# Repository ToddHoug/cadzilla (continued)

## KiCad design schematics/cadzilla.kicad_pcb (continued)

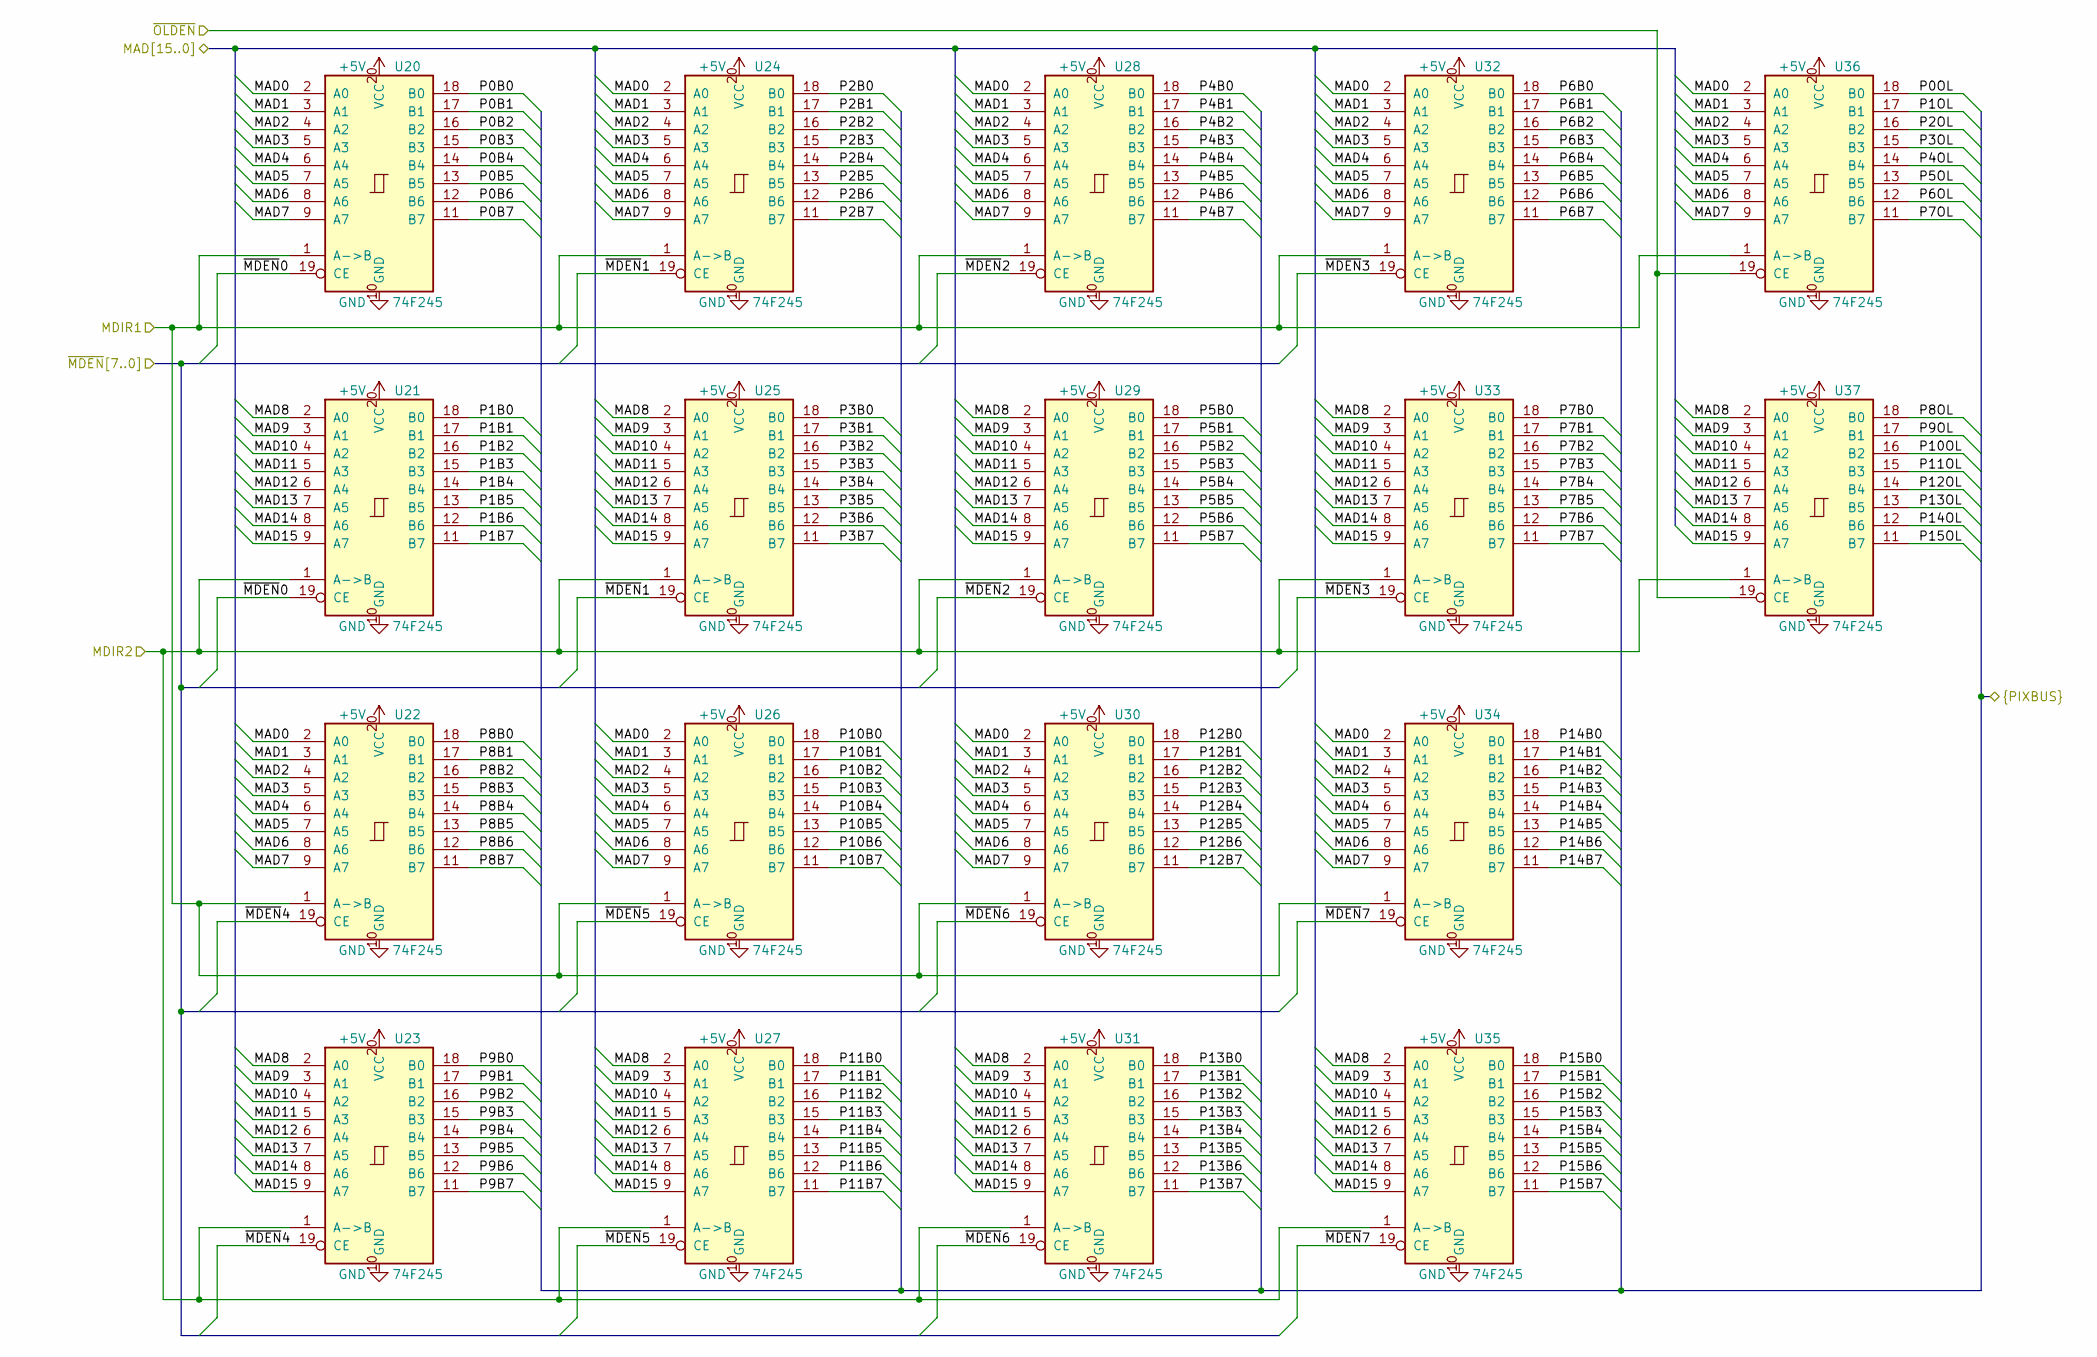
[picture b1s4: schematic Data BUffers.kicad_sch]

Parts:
U20, U21, U22, U23, U24, U25, U26, U27, U28, U29, U30, U31, U32, U33, U34, U35, U36, U37: 74F245; DIP-20_W7.62mm_Socket

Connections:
+5V: U20.20 (VCC), U21.20 (VCC), U22.20 (VCC), U23.20 (VCC), U24.20 (VCC), U25.20 (VCC), U26.20 (VCC), U27.20 (VCC), U28.20 (VCC), U29.20 (VCC), U30.20 (VCC), U31.20 (VCC), U32.20 (VCC), U33.20 (VCC), U34.20 (VCC), U35.20 (VCC), U36.20 (VCC), U37.20 (VCC); also elsewhere on the board
/Data Buffers/MAD0: U20.2 (A0), U22.2 (A0), U24.2 (A0), U26.2 (A0), U28.2 (A0), U30.2 (A0), U32.2 (A0), U34.2 (A0), U36.2 (A0); also elsewhere on the board
/Data Buffers/MAD1: U20.3 (A1), U22.3 (A1), U24.3 (A1), U26.3 (A1), U28.3 (A1), U30.3 (A1), U32.3 (A1), U34.3 (A1), U36.3 (A1); also elsewhere on the board
/Data Buffers/MAD2: U20.4 (A2), U22.4 (A2), U24.4 (A2), U26.4 (A2), U28.4 (A2), U30.4 (A2), U32.4 (A2), U34.4 (A2), U36.4 (A2); also elsewhere on the board
/Data Buffers/MAD3: U20.5 (A3), U22.5 (A3), U24.5 (A3), U26.5 (A3), U28.5 (A3), U30.5 (A3), U32.5 (A3), U34.5 (A3), U36.5 (A3); also elsewhere on the board
/Data Buffers/MAD4: U20.6 (A4), U22.6 (A4), U24.6 (A4), U26.6 (A4), U28.6 (A4), U30.6 (A4), U32.6 (A4), U34.6 (A4), U36.6 (A4); also elsewhere on the board
/Data Buffers/MAD5: U20.7 (A5), U22.7 (A5), U24.7 (A5), U26.7 (A5), U28.7 (A5), U30.7 (A5), U32.7 (A5), U34.7 (A5), U36.7 (A5); also elsewhere on the board
/Data Buffers/MAD6: U20.8 (A6), U22.8 (A6), U24.8 (A6), U26.8 (A6), U28.8 (A6), U30.8 (A6), U32.8 (A6), U34.8 (A6), U36.8 (A6); also elsewhere on the board
/Data Buffers/MAD7: U20.9 (A7), U22.9 (A7), U24.9 (A7), U26.9 (A7), U28.9 (A7), U30.9 (A7), U32.9 (A7), U34.9 (A7), U36.9 (A7); also elsewhere on the board
/Data Buffers/MAD8: U21.2 (A0), U23.2 (A0), U25.2 (A0), U27.2 (A0), U29.2 (A0), U31.2 (A0), U33.2 (A0), U35.2 (A0), U37.2 (A0); also elsewhere on the board
/Data Buffers/MAD9: U21.3 (A1), U23.3 (A1), U25.3 (A1), U27.3 (A1), U29.3 (A1), U31.3 (A1), U33.3 (A1), U35.3 (A1), U37.3 (A1); also elsewhere on the board
/Data Buffers/MAD10: U21.4 (A2), U23.4 (A2), U25.4 (A2), U27.4 (A2), U29.4 (A2), U31.4 (A2), U33.4 (A2), U35.4 (A2), U37.4 (A2); also elsewhere on the board
/Data Buffers/MAD11: U21.5 (A3), U23.5 (A3), U25.5 (A3), U27.5 (A3), U29.5 (A3), U31.5 (A3), U33.5 (A3), U35.5 (A3), U37.5 (A3); also elsewhere on the board
/Data Buffers/MAD12: U21.6 (A4), U23.6 (A4), U25.6 (A4), U27.6 (A4), U29.6 (A4), U31.6 (A4), U33.6 (A4), U35.6 (A4), U37.6 (A4); also elsewhere on the board
/Data Buffers/MAD13: U21.7 (A5), U23.7 (A5), U25.7 (A5), U27.7 (A5), U29.7 (A5), U31.7 (A5), U33.7 (A5), U35.7 (A5), U37.7 (A5); also elsewhere on the board
/Data Buffers/MAD14: U21.8 (A6), U23.8 (A6), U25.8 (A6), U27.8 (A6), U29.8 (A6), U31.8 (A6), U33.8 (A6), U35.8 (A6), U37.8 (A6); also elsewhere on the board
/Data Buffers/MAD15: U21.9 (A7), U23.9 (A7), U25.9 (A7), U27.9 (A7), U29.9 (A7), U31.9 (A7), U33.9 (A7), U35.9 (A7), U37.9 (A7); also elsewhere on the board
/Data Buffers/P0B0: U20.18 (B0); also elsewhere on the board
/Data Buffers/P0B1: U20.17 (B1); also elsewhere on the board
/Data Buffers/P0B2: U20.16 (B2); also elsewhere on the board
/Data Buffers/P0B3: U20.15 (B3); also elsewhere on the board
/Data Buffers/P0B4: U20.14 (B4); also elsewhere on the board
/Data Buffers/P0B5: U20.13 (B5); also elsewhere on the board
/Data Buffers/P0B6: U20.12 (B6); also elsewhere on the board
/Data Buffers/P0B7: U20.11 (B7); also elsewhere on the board
/Data Buffers/P0OL: U36.18 (B0); also elsewhere on the board
/Data Buffers/P1B0: U21.18 (B0); also elsewhere on the board
/Data Buffers/P1B1: U21.17 (B1); also elsewhere on the board
/Data Buffers/P1B2: U21.16 (B2); also elsewhere on the board
/Data Buffers/P1B3: U21.15 (B3); also elsewhere on the board
/Data Buffers/P1B4: U21.14 (B4); also elsewhere on the board
/Data Buffers/P1B5: U21.13 (B5); also elsewhere on the board
/Data Buffers/P1B6: U21.12 (B6); also elsewhere on the board
/Data Buffers/P1B7: U21.11 (B7); also elsewhere on the board
/Data Buffers/P1OL: U36.17 (B1); also elsewhere on the board
/Data Buffers/P2B0: U24.18 (B0); also elsewhere on the board
/Data Buffers/P2B1: U24.17 (B1); also elsewhere on the board
/Data Buffers/P2B2: U24.16 (B2); also elsewhere on the board
/Data Buffers/P2B3: U24.15 (B3); also elsewhere on the board
/Data Buffers/P2B4: U24.14 (B4); also elsewhere on the board
/Data Buffers/P2B5: U24.13 (B5); also elsewhere on the board
/Data Buffers/P2B6: U24.12 (B6); also elsewhere on the board
/Data Buffers/P2B7: U24.11 (B7); also elsewhere on the board
/Data Buffers/P2OL: U36.16 (B2); also elsewhere on the board
/Data Buffers/P3B0: U25.18 (B0); also elsewhere on the board
/Data Buffers/P3B1: U25.17 (B1); also elsewhere on the board
/Data Buffers/P3B2: U25.16 (B2); also elsewhere on the board
/Data Buffers/P3B3: U25.15 (B3); also elsewhere on the board
/Data Buffers/P3B4: U25.14 (B4); also elsewhere on the board
/Data Buffers/P3B5: U25.13 (B5); also elsewhere on the board
/Data Buffers/P3B6: U25.12 (B6); also elsewhere on the board
/Data Buffers/P3B7: U25.11 (B7); also elsewhere on the board
/Data Buffers/P3OL: U36.15 (B3); also elsewhere on the board
/Data Buffers/P4B0: U28.18 (B0); also elsewhere on the board
/Data Buffers/P4B1: U28.17 (B1); also elsewhere on the board
/Data Buffers/P4B2: U28.16 (B2); also elsewhere on the board
/Data Buffers/P4B3: U28.15 (B3); also elsewhere on the board
/Data Buffers/P4B4: U28.14 (B4); also elsewhere on the board
/Data Buffers/P4B5: U28.13 (B5); also elsewhere on the board
/Data Buffers/P4B6: U28.12 (B6); also elsewhere on the board
/Data Buffers/P4B7: U28.11 (B7); also elsewhere on the board
/Data Buffers/P4OL: U36.14 (B4); also elsewhere on the board
/Data Buffers/P5B0: U29.18 (B0); also elsewhere on the board
/Data Buffers/P5B1: U29.17 (B1); also elsewhere on the board
/Data Buffers/P5B2: U29.16 (B2); also elsewhere on the board
/Data Buffers/P5B3: U29.15 (B3); also elsewhere on the board
/Data Buffers/P5B4: U29.14 (B4); also elsewhere on the board
/Data Buffers/P5B5: U29.13 (B5); also elsewhere on the board
/Data Buffers/P5B6: U29.12 (B6); also elsewhere on the board
/Data Buffers/P5B7: U29.11 (B7); also elsewhere on the board
/Data Buffers/P5OL: U36.13 (B5); also elsewhere on the board
/Data Buffers/P6B0: U32.18 (B0); also elsewhere on the board
/Data Buffers/P6B1: U32.17 (B1); also elsewhere on the board
/Data Buffers/P6B2: U32.16 (B2); also elsewhere on the board
/Data Buffers/P6B3: U32.15 (B3); also elsewhere on the board
/Data Buffers/P6B4: U32.14 (B4); also elsewhere on the board
/Data Buffers/P6B5: U32.13 (B5); also elsewhere on the board
/Data Buffers/P6B6: U32.12 (B6); also elsewhere on the board
/Data Buffers/P6B7: U32.11 (B7); also elsewhere on the board
/Data Buffers/P6OL: U36.12 (B6); also elsewhere on the board
/Data Buffers/P7B0: U33.18 (B0); also elsewhere on the board
/Data Buffers/P7B1: U33.17 (B1); also elsewhere on the board
/Data Buffers/P7B2: U33.16 (B2); also elsewhere on the board
/Data Buffers/P7B3: U33.15 (B3); also elsewhere on the board
/Data Buffers/P7B4: U33.14 (B4); also elsewhere on the board
/Data Buffers/P7B5: U33.13 (B5); also elsewhere on the board
/Data Buffers/P7B6: U33.12 (B6); also elsewhere on the board
/Data Buffers/P7B7: U33.11 (B7); also elsewhere on the board
/Data Buffers/P7OL: U36.11 (B7); also elsewhere on the board
/Data Buffers/P8B0: U22.18 (B0); also elsewhere on the board
/Data Buffers/P8B1: U22.17 (B1); also elsewhere on the board
/Data Buffers/P8B2: U22.16 (B2); also elsewhere on the board
/Data Buffers/P8B3: U22.15 (B3); also elsewhere on the board
/Data Buffers/P8B4: U22.14 (B4); also elsewhere on the board
/Data Buffers/P8B5: U22.13 (B5); also elsewhere on the board
/Data Buffers/P8B6: U22.12 (B6); also elsewhere on the board
/Data Buffers/P8B7: U22.11 (B7); also elsewhere on the board
/Data Buffers/P8OL: U37.18 (B0); also elsewhere on the board
/Data Buffers/P9B0: U23.18 (B0); also elsewhere on the board
/Data Buffers/P9B1: U23.17 (B1); also elsewhere on the board
/Data Buffers/P9B2: U23.16 (B2); also elsewhere on the board
/Data Buffers/P9B3: U23.15 (B3); also elsewhere on the board
/Data Buffers/P9B4: U23.14 (B4); also elsewhere on the board
/Data Buffers/P9B5: U23.13 (B5); also elsewhere on the board
/Data Buffers/P9B6: U23.12 (B6); also elsewhere on the board
/Data Buffers/P9B7: U23.11 (B7); also elsewhere on the board
/Data Buffers/P9OL: U37.17 (B1); also elsewhere on the board
/Data Buffers/P10B0: U26.18 (B0); also elsewhere on the board
/Data Buffers/P10B1: U26.17 (B1); also elsewhere on the board
/Data Buffers/P10B2: U26.16 (B2); also elsewhere on the board
/Data Buffers/P10B3: U26.15 (B3); also elsewhere on the board
/Data Buffers/P10B4: U26.14 (B4); also elsewhere on the board
/Data Buffers/P10B5: U26.13 (B5); also elsewhere on the board
/Data Buffers/P10B6: U26.12 (B6); also elsewhere on the board
/Data Buffers/P10B7: U26.11 (B7); also elsewhere on the board
/Data Buffers/P10OL: U37.16 (B2); also elsewhere on the board
/Data Buffers/P11B0: U27.18 (B0); also elsewhere on the board
/Data Buffers/P11B1: U27.17 (B1); also elsewhere on the board
/Data Buffers/P11B2: U27.16 (B2); also elsewhere on the board
/Data Buffers/P11B3: U27.15 (B3); also elsewhere on the board
/Data Buffers/P11B4: U27.14 (B4); also elsewhere on the board
/Data Buffers/P11B5: U27.13 (B5); also elsewhere on the board
/Data Buffers/P11B6: U27.12 (B6); also elsewhere on the board
/Data Buffers/P11B7: U27.11 (B7); also elsewhere on the board
/Data Buffers/P11OL: U37.15 (B3); also elsewhere on the board
/Data Buffers/P12B0: U30.18 (B0); also elsewhere on the board
/Data Buffers/P12B1: U30.17 (B1); also elsewhere on the board
/Data Buffers/P12B2: U30.16 (B2); also elsewhere on the board
/Data Buffers/P12B3: U30.15 (B3); also elsewhere on the board
/Data Buffers/P12B4: U30.14 (B4); also elsewhere on the board
/Data Buffers/P12B5: U30.13 (B5); also elsewhere on the board
/Data Buffers/P12B6: U30.12 (B6); also elsewhere on the board
/Data Buffers/P12B7: U30.11 (B7); also elsewhere on the board
/Data Buffers/P12OL: U37.14 (B4); also elsewhere on the board
/Data Buffers/P13B0: U31.18 (B0); also elsewhere on the board
/Data Buffers/P13B1: U31.17 (B1); also elsewhere on the board
/Data Buffers/P13B2: U31.16 (B2); also elsewhere on the board
/Data Buffers/P13B3: U31.15 (B3); also elsewhere on the board
/Data Buffers/P13B4: U31.14 (B4); also elsewhere on the board
/Data Buffers/P13B5: U31.13 (B5); also elsewhere on the board
/Data Buffers/P13B6: U31.12 (B6); also elsewhere on the board
/Data Buffers/P13B7: U31.11 (B7); also elsewhere on the board
/Data Buffers/P13OL: U37.13 (B5); also elsewhere on the board
/Data Buffers/P14B0: U34.18 (B0); also elsewhere on the board
/Data Buffers/P14B1: U34.17 (B1); also elsewhere on the board
/Data Buffers/P14B2: U34.16 (B2); also elsewhere on the board
/Data Buffers/P14B3: U34.15 (B3); also elsewhere on the board
/Data Buffers/P14B4: U34.14 (B4); also elsewhere on the board
/Data Buffers/P14B5: U34.13 (B5); also elsewhere on the board
/Data Buffers/P14B6: U34.12 (B6); also elsewhere on the board
/Data Buffers/P14B7: U34.11 (B7); also elsewhere on the board
/Data Buffers/P14OL: U37.12 (B6); also elsewhere on the board
/Data Buffers/P15B0: U35.18 (B0); also elsewhere on the board
/Data Buffers/P15B1: U35.17 (B1); also elsewhere on the board
/Data Buffers/P15B2: U35.16 (B2); also elsewhere on the board
/Data Buffers/P15B3: U35.15 (B3); also elsewhere on the board
/Data Buffers/P15B4: U35.14 (B4); also elsewhere on the board
/Data Buffers/P15B5: U35.13 (B5); also elsewhere on the board
/Data Buffers/P15B6: U35.12 (B6); also elsewhere on the board
/Data Buffers/P15B7: U35.11 (B7); also elsewhere on the board
/Data Buffers/P15OL: U37.11 (B7); also elsewhere on the board
/Data Buffers/~MDEN0: U20.19 (CE), U21.19 (CE); also elsewhere on the board
/Data Buffers/~MDEN1: U24.19 (CE), U25.19 (CE); also elsewhere on the board
/Data Buffers/~MDEN2: U28.19 (CE), U29.19 (CE); also elsewhere on the board
/Data Buffers/~MDEN3: U32.19 (CE), U33.19 (CE); also elsewhere on the board
/Data Buffers/~MDEN4: U22.19 (CE), U23.19 (CE); also elsewhere on the board
/Data Buffers/~MDEN5: U26.19 (CE), U27.19 (CE); also elsewhere on the board
/Data Buffers/~MDEN6: U30.19 (CE), U31.19 (CE); also elsewhere on the board
/Data Buffers/~MDEN7: U34.19 (CE), U35.19 (CE); also elsewhere on the board
/Memory Interface/MDIR1: U20.1 (A->B), U22.1 (A->B), U24.1 (A->B), U26.1 (A->B), U28.1 (A->B), U30.1 (A->B), U32.1 (A->B), U34.1 (A->B), U36.1 (A->B); also elsewhere on the board
/Memory Interface/MDIR2: U21.1 (A->B), U23.1 (A->B), U25.1 (A->B), U27.1 (A->B), U29.1 (A->B), U31.1 (A->B), U33.1 (A->B), U35.1 (A->B), U37.1 (A->B); also elsewhere on the board
/Memory Interface/~OLDEN: U36.19 (CE), U37.19 (CE); also elsewhere on the board
GND: U20.10 (GND), U21.10 (GND), U22.10 (GND), U23.10 (GND), U24.10 (GND), U25.10 (GND), U26.10 (GND), U27.10 (GND), U28.10 (GND), U29.10 (GND), U30.10 (GND), U31.10 (GND), U32.10 (GND), U33.10 (GND), U34.10 (GND), U35.10 (GND), U36.10 (GND), U37.10 (GND); also elsewhere on the board

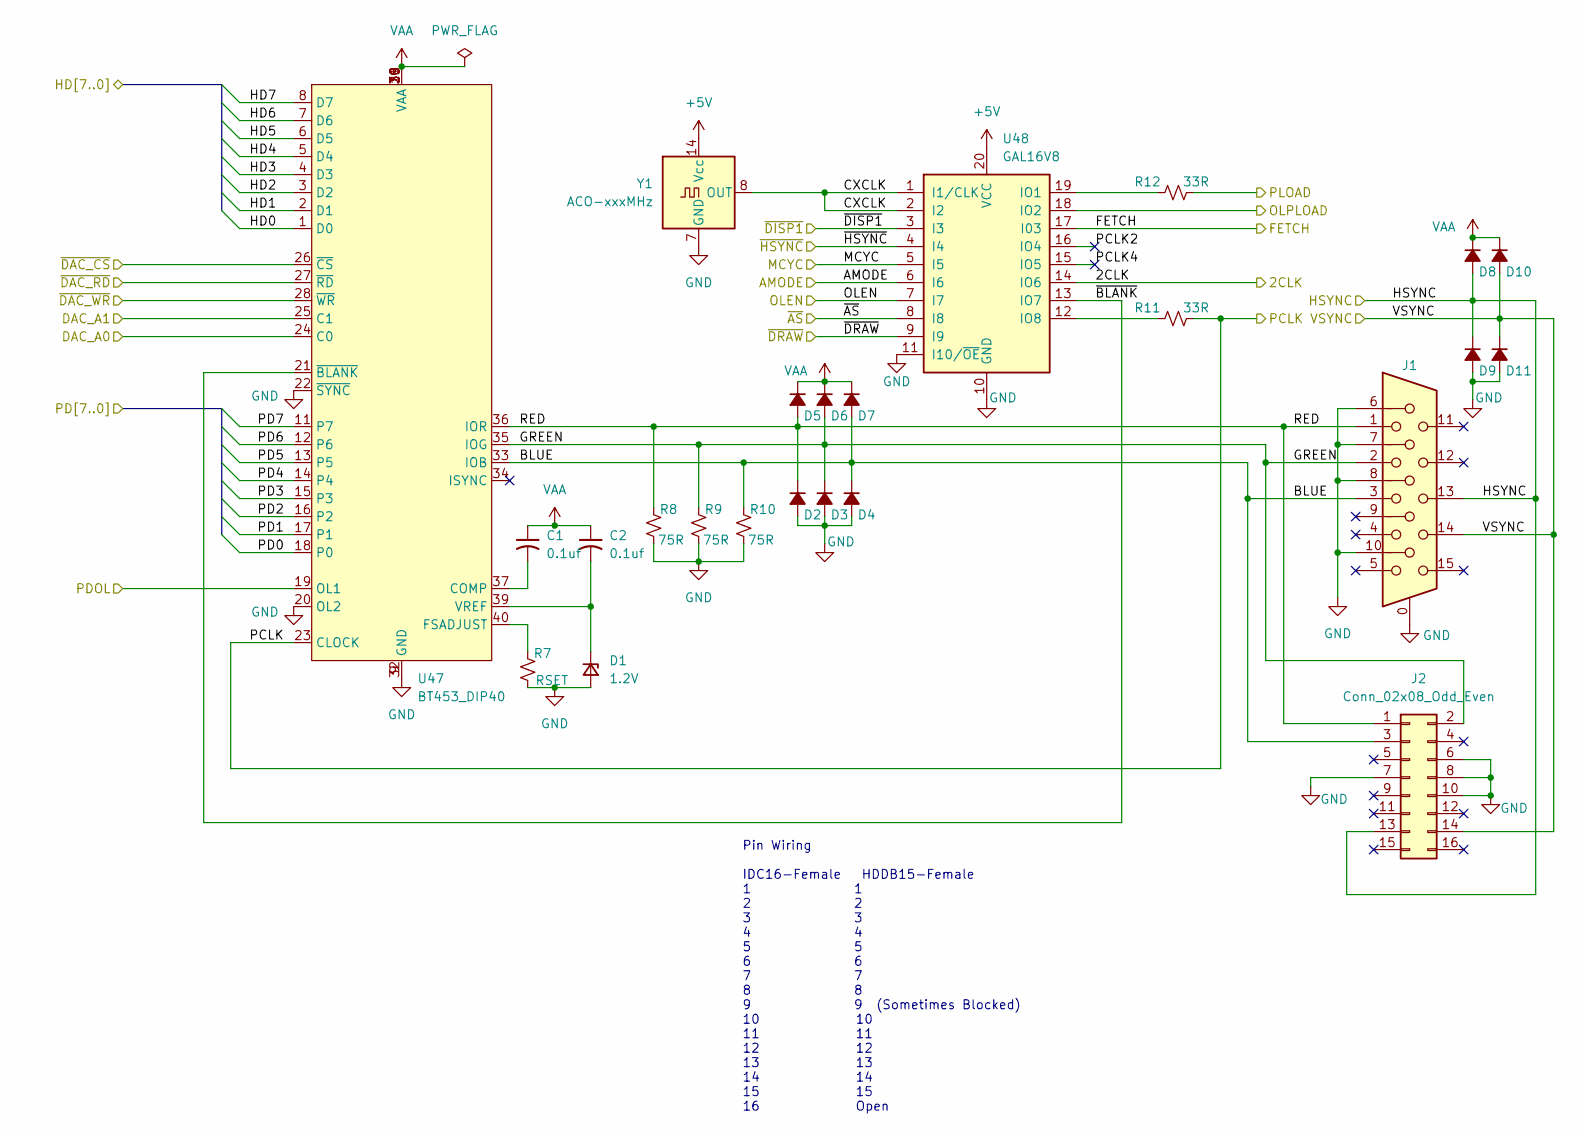
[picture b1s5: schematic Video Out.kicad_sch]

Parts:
C1, C2: 0.1uf; C_Rect_L9.1mm_W2.5mm_P7.62mm_MKT
D1: 1.2V; D_A-405_P7.62mm_Horizontal
D2, D3, D4, D5, D6, D7, D8, D9, D10, D11: 1N4148; D_0805_2012Metric_Pad1.15x1.40mm_HandSolder
J1: DE15_Socket_HighDensity; DSUB-15-HD_Socket_Horizontal_P2.29x1.90mm_EdgePinOffset3.03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
J2: Conn_02x08_Odd_Even; PinHeader_2x08_P2.54mm_Vertical
R7: RSET; R_Axial_DIN0204_L3.6mm_D1.6mm_P7.62mm_Horizontal
R8, R9, R10: 75R; R_Axial_DIN0204_L3.6mm_D1.6mm_P7.62mm_Horizontal
R11, R12: 33R; R_Axial_DIN0204_L3.6mm_D1.6mm_P7.62mm_Horizontal
U47: BT453_DIP40; DIP-40_W15.24mm_Socket
U48: GAL16V8; DIP-20_W7.62mm_Socket
Y1: ACO-xxxMHz; Oscillator_DIP-14

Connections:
+5V: U48.20 (VCC), Y1.14 (Vcc); also elsewhere on the board
/2CLK: U48.14 (IO6); also elsewhere on the board
/MCYC: U48.5 (I5); also elsewhere on the board
/Memory Interface/FETCH: U48.17 (I03); also elsewhere on the board
/S100 Interface/AMODE: U48.6 (I6); also elsewhere on the board
/S100 Interface/DAC_A0: U47.24 (C0); also elsewhere on the board
/S100 Interface/DAC_A1: U47.25 (C1); also elsewhere on the board
/S100 Interface/HD0: U47.1 (D0); also elsewhere on the board
/S100 Interface/HD1: U47.2 (D1); also elsewhere on the board
/S100 Interface/HD2: U47.3 (D2); also elsewhere on the board
/S100 Interface/HD3: U47.4 (D3); also elsewhere on the board
/S100 Interface/HD4: U47.5 (D4); also elsewhere on the board
/S100 Interface/HD5: U47.6 (D5); also elsewhere on the board
/S100 Interface/HD6: U47.7 (D6); also elsewhere on the board
/S100 Interface/HD7: U47.8 (D7); also elsewhere on the board
/S100 Interface/HSYNC: D8.2 (A), D9.1 (K), J1.13, J2.13; also elsewhere on the board
/S100 Interface/OLEN: U48.7 (I7); also elsewhere on the board
/S100 Interface/VSYNC: D10.2 (A), D11.1 (K), J1.14, J2.14; also elsewhere on the board
/S100 Interface/~DAC_CS: U47.26 (~CS); also elsewhere on the board
/S100 Interface/~DAC_RD: U47.27 (~RD); also elsewhere on the board
/S100 Interface/~DAC_WR: U47.28 (~WR); also elsewhere on the board
/Shift Registers/OLPLOAD: U48.18 (IO2); also elsewhere on the board
/Shift Registers/PCLK: R11.2, U47.23 (CLOCK); also elsewhere on the board
/Shift Registers/PD0: U47.18 (P0); also elsewhere on the board
/Shift Registers/PD1: U47.17 (P1); also elsewhere on the board
/Shift Registers/PD2: U47.16 (P2); also elsewhere on the board
/Shift Registers/PD3: U47.15 (P3); also elsewhere on the board
/Shift Registers/PD4: U47.14 (P4); also elsewhere on the board
/Shift Registers/PD5: U47.13 (P5); also elsewhere on the board
/Shift Registers/PD6: U47.12 (P6); also elsewhere on the board
/Shift Registers/PD7: U47.11 (P7); also elsewhere on the board
/Shift Registers/PDOL: U47.19 (OL1); also elsewhere on the board
/Shift Registers/PLOAD: R12.2; also elsewhere on the board
/Video Out/BLUE: D4.1 (K), D7.2 (A), J1.3, J2.3, R10.1, U47.33 (IOB)
/Video Out/CXCLK: U48.1 (I1/CLK), U48.2 (I2), Y1.8 (OUT)
/Video Out/GREEN: D3.1 (K), D6.2 (A), J1.2, J2.2, R9.1, U47.35 (IOG)
/Video Out/PCLK2: U48.16 (IO4)
/Video Out/PCLK4: U48.15 (IO5)
/Video Out/RED: D2.1 (K), D5.2 (A), J1.1, J2.1, R8.1, U47.36 (IOR)
/Video Out/~BLANK: U47.21 (~BLANK), U48.13 (IO7)
/Video Out/~DISP1: U48.3 (I3); also elsewhere on the board
/~AS: U48.8 (I8); also elsewhere on the board
/~DRAW: U48.9 (I9); also elsewhere on the board
/~HSYNC: U48.4 (I4); also elsewhere on the board
GND: D1.2 (A), D2.2 (A), D3.2 (A), D4.2 (A), D9.2 (A), D11.2 (A), J1.0, J1.6, J1.7, J1.8, J1.10, J2.6, J2.7, J2.8, J2.10, R7.2, R8.2, R9.2, R10.2, U47.9 (GND), U47.20 (OL2), U47.22 (~SYNC), U47.32 (GND), U48.10 (GND), U48.11 (I10/~OE), Y1.7 (GND); also elsewhere on the board
unnamed: C2.2, D1.1 (K), U47.39 (VREF)
unnamed: C1.2, U47.37 (COMP)
unnamed: R7.1, U47.40 (FSADJUST)
unnamed: R12.1, U48.19 (IO1)
unnamed: R11.1, U48.12 (IO8)
VAA: C1.1, C2.1, D5.1 (K), D6.1 (K), D7.1 (K), D8.1 (K), D10.1 (K), U47.10 (VAA), U47.29 (VAA), U47.30 (VAA), U47.31 (VAA), U47.38 (VAA); also elsewhere on the board

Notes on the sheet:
Pin Wiring IDC16-Female HDDB15-Female 1 1 2 2 3 3 4 4 5 5 6 6 7 7 8 8 9 9 (Sometimes Blocked) 10 10 11 11 12 12 13 13 14 14 15 15 16 Open
